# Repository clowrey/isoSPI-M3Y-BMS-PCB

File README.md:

# CellKeeper BMS — Rev1

KiCad PCB design for the **CellKeeper Battery Management System**, a replacement BMS controller for battery packs using the isoSPI protocol.

## Overview

- **MCU:** Raspberry Pi RP2354B (dual Cortex-M33 @ 150 MHz)
- **Current sensing:** TI INA228 (20-bit ADC, shunt-based)
- **Pack voltage:** 6-channel monitoring via precision dividers
- **BMB communication:** isoSPI master with galvanic isolation (Manchester encoding via PIO)
- **CAN bus:** 500 kbps, hardware transceiver
- **Contactor control:** 4-channel PWM outputs with inrush limiting
- **Input:** 12 V nominal; rated for up to 400 V DC pack voltage

## Repository Contents

| Path | Description |
|------|-------------|
| `CellKeeper.kicad_pro` | KiCad project file |
| `CellKeeper.kicad_sch` | Schematic |
| `CellKeeper.kicad_pcb` | PCB layout |
| `CellKeeper_Local.kicad_sym` / `CellKeeper_Local.pretty/` | Local symbol and footprint libraries |
| `CellKeeper.3dshapes/` | 3D models |
| `graphics/` | Silkscreen artwork and images |
| `production/` | Manufacturing outputs |
| `python_scripts/` | Utility scripts |

## Getting Started

1. Install [KiCad 10.0+](https://www.kicad.org/download/)
2. Clone this repository
3. Open `CellKeeper.kicad_pro` — project libraries load from the local `sym-lib-table` and `fp-lib-table`

## Safety

⚠️ This board interfaces with 400 V battery packs that can deliver **lethal** current. Only qualified personnel should work on high-voltage systems. This is a Rev1 development design — untested, no warranty, use at your own risk.

## Acknowledgments

- **Damien Maguire & Tom de Bree** — Original BATMan BMS software

## License

GPL-3.0 — see [LICENSE](LICENSE).

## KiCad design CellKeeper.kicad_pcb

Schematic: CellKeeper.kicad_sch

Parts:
1/2V1, 3v1, 5V1: TP; BMS_Library__TestPoint_THTPad_D1.5mm_Drill1.0mm
A1: RaspberryPi_Pico; Module__RaspberryPi_Pico_Common_Unspecified
BT1, BT2, BT3, BT4, BT5, BT6, BT7, BT8: ~100V Brick
C1, C14, C31: 680uF; Capacitor_THT__CP_Radial_D10.0mm_P5.00mm; Voltage 35V Polymer; JLCPCB Part # C46550429
C2, C10, C11, C13, C15, C16, C18, C22, C23, C28, C29, C30, C34, C35, C36, C54, C60, C89, C91, C104, C105, C106, C114: 100nF; Capacitor_SMD__C_0603_1608Metric; JLCPCB Part # C14663
C3, C4, C6, C8, C17, C32: 10uF; Capacitor_SMD__C_0805_2012Metric; Voltage 50V; JLCPCB Part # C440198
C5, C7, C12, C33, C37, C48, C49, C69: 22uF; Capacitor_SMD__C_0805_2012Metric; Voltage 25V X5R; JLCPCB Part # C45783
C9: 4.7uF; Capacitor_SMD__C_0603_1608Metric; JLCPCB Part # C19666
C19, C20, C41, C42, C67, C96, C97, C98, C99, C109, C110, C111, C112: 1uF; Capacitor_SMD__C_0603_1608Metric; JLCPCB Part # C15849
C21, C55, C116: 10uF; Capacitor_SMD__C_0805_2012Metric; Voltage 50V X5R; JLCPCB Part # C440198
C24, C25, C26, C27, C103, C113: 100pF; Capacitor_SMD__C_0603_1608Metric; JLCPCB Part # C14858
C38, C43, C68, C72: 4.7u; RP2350_80QFN_minimal__C_0402_1005Metric_small_pads; JLCPCB Part # C23733
C39, C40, C70, C71: 15pF; Capacitor_SMD__C_0402_1005Metric; JLCPCB Part # C1548
C44, C46, C47, C50, C51, C53, C56, C58, C59, C61, C63, C65, C75, C83, C84, C85, C86, C88, C90, C92, C93, C100, C101, C102: 100n; Capacitor_SMD__C_0402_1005Metric; JLCPCB Part # C1525
C45, C52, C82, C87: 4.7u; Capacitor_SMD__C_0402_1005Metric; JLCPCB Part # C23733
C62, C64: 100nf; Capacitor_SMD__C_0603_1608Metric_Pad1.08x0.95mm_HandSolder; JLCPCB Part # C14663
C66: 10uF; Capacitor_SMD__C_0805_2012Metric_Pad1.18x1.45mm_HandSolder; Voltage 50V; JLCPCB Part # C440198
C73, C74: 100nF; Capacitor_SMD__C_0603_1608Metric_Pad1.08x0.95mm_HandSolder; JLCPCB Part # C14663
C76, C77, C78, C79, C80, C81: 100nf; Capacitor_SMD__C_0603_1608Metric; JLCPCB Part # C14663
C94, C95, C107, C108: 1nF; Capacitor_SMD__C_1206_3216Metric; JLCPCB Part # C9196
Cell1, Cell2, Cell3: Battery_Cell
D1, D2, D3, D4, D5, D6, D24, D25, D26, D28, D29, D30, D31: SMB6.8CA; Diode_SMD__D_SMB; JLCPCB Part # C78395
D7, D8, D14, D19, D32, D35, D36, D43, D48: Green; LED_SMD__LED_0805_2012Metric; JLCPCB Part # C2297
D9, D10, D27, D41, D46, D49: Red; LED_SMD__LED_0805_2012Metric; JLCPCB Part # C84256
D11, D12, D15, D16, D20, D23, D37, D38, D42, D44, D47, D50: SS54; Diode_SMD__D_SMA; JLCPCB Part # C22452
D13, D17, D22, D33, D34, D45: White; LED_SMD__LED_0805_2012Metric; JLCPCB Part # C34499
D18, D21, D39, D40: SMCJ33CA; Diode_SMD__D_SMC; JLCPCB Part # C224050
F1, F3: Pyro Fuse
F2, F4: 63A HV DC
FB1, FB3, FB5: 600R@100MHz; Inductor_SMD__L_0603_1608Metric_Pad1.05x0.95mm_HandSolder; JLCPCB Part # C1002
FB2: 120Ω@100MHz; Capacitor_SMD__C_0603_1608Metric; JLCPCB Part # C14709
FL1, FL2: SDCW3225S-2-102TF; BMS_Library__FILTER-SMD_4P-L3.2-W2.5-BL; JLCPCB Part # C192586
GND1: TP; BMS_Library__TestPoint_THTPad_D1.5mm_Drill1.0mm
GPIO1, GPIO2, GPIO3: TP; BMS_Library__TestPoint_THTPad_D1.5mm_Drill1.0mm
H1, H2: MountingHole_Pad; MountingHole__MountingHole_3.7mm; not fitted
H3, H4: MountingHole_Pad; MountingHole__MountingHole_5mm; not fitted
H5, H6, H7, H8, H9, H10, H11, H12, H13: Mouse Bites 2mm; BMS_Library__mouse-bite-2mm-slot-min
H14, H15: MountingHole_Pad; MountingHole__MountingHole_8.4mm_M8_Pad_Via
J1: Screw_Terminal_01x04; BMS_Library__PhoenixContact_MC_1_5_4-G-3.81_1x04_P3.81mm_Ho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
J2: Screw_Terminal_01x01; BMS_Library__XFCN_T34008_M3_Terminal_Frame_PCB; JLCPCB Part # C481446
J3, J7, J15: Screw_Terminal_01x04; BMS_Library__PhoenixContact_MC_1_5_4-G-3.81_1x04_P3.81mm_Ho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; not fitted
J4, J5: 8P8C_LED_Shielded_x2; Connector_RJ__RJ45_HCTL_HC-RJ45-5JA-2-2-Y; JLCPCB Part # C3010546
J6: OEM Connector; BMS_Library__S44BRAD1AK; Mfr. # S44B-RAD1AK
J8, J16: Conn_01x03; Connector_PinHeader_2.54mm__PinHeader_1x03_P2.54mm_Vertical; not fitted
J9, J11, J19: USB_C_Receptacle_USB2.0_16P; BMS_Library__USB_C_Receptacle_HRO_TYPE-C-31-M-12; JLCPCB Part # C2765186
J10: 3.81P Screw Terminal; BMS_Library__PhoenixContact_MC_1_5_8-G-3.81_1x08_P3.81mm_Ho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; not fitted
J12, J22: Conn_02x10_Odd_Even; Connector_PinHeader_2.54mm__PinHeader_2x10_P2.54mm_Vertical; not fitted
J13: USB_C_Receptacle_USB2.0_16P
J14: OEM Shunt Connector; BMS_Library__CONN_ZE05H-8DP-2H_HIR; MFR.Part # ZE05H-8DP-2H; JLCPCB Part # C17284895
J17: OEM HV Sense Connector; BMS_Library__CONN_173864-1_TYC_Empty_Pins; MFR Part # 173864-1; JLCPCB Part # C573648
J18: 7.62mm Pitch Screw Terminal; Connector_Phoenix_GMSTB__PhoenixContact_GMSTBA_2_5_6-G-7_62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; not fitted
J20, J23: OEM Connector; BMS_Library__CONN_SD-34912-001_02_MOL; MFR.Part # 349128020; JLCPCB Part # C587318
J21, J24: 3.81P Screw Terminal; BMS_Library__PhoenixContact_MC_1_5_2-G-3.81_1x02_P3.81mm_Ho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; not fitted
JP1, JP2, JP3, JP4, JP7, JP8, JP9, JP12, JP13, JP14, JP16, JP17, JP18, JP19, JP20, JP21, JP22, JP23, JP24, JP27, JP28, JP29, JP30, JP31, JP32, JP33, JP34, JP35, JP37: 0r; BMS_Library__J_0603_jumper; JLCPCB Part # C21189; not fitted
JP5, JP6, JP10, JP11, JP15, JP36: 0r; BMS_Library__J_0603_jumper; JLCPCB Part # C21189
JP25, JP26: jumper-bridged; Jumper__SolderJumper-2_P1.3mm_Bridged_RoundedPad1.0x1.5mm
K1, K6: Link Positive
K2, K7: Link Negative
K3, K9: FC Positive
K4, K8: FC Negative
K5, K10: Inverter
L1, L5: 6.8uh; Inductor_SMD__L_Changjiang_FXL0630; JLCPCB Part # C167221
L2, L3: 22uh 5.5A; Inductor_SMD__L_Changjiang_FXL1040; JLCPCB Part # C475917
L4, L6: 3.3uh; RP2350_80QFN_minimal__L_pol_2016; JLCPCB Part # C42411119
Q1, Q2, Q3, Q4: BSC0805LS; BMS_Library__TDSON-8_5x6_; JLCPCB Part # C534374
R1, R2, R11, R16, R29, R33, R35, R39, R40, R41, R96, R97, R98, R99, R100, R101, R140: 24k; Resistor_SMD__R_0603_1608Metric; JLCPCB Part # C23352
R3, R4, R15, R17, R19, R20, R21, R25, R28, R42, R50, R84: 10k; Resistor_SMD__R_0603_1608Metric; JLCPCB Part # C25804
R5, R10, R18, R24, R34, R36, R151, R152: 100k; Resistor_SMD__R_0603_1608Metric; JLCPCB Part # C25803
R7, R12, R37, R38: 33R; Resistor_SMD__R_0603_1608Metric; JLCPCB Part # C23140
R8, R9, R22, R23, R46, R47, R48, R49, R133, R134, R141: 1k; Resistor_SMD__R_0603_1608Metric; JLCPCB Part # C21190
R13, R14, R51, R52: 10k; Resistor_SMD__R_0603_1608Metric_Pad0.98x0.95mm_HandSolder; JLCPCB Part # C25804
R26: 3.3k; Resistor_SMD__R_0402_1005Metric; JLCPCB Part # C25890
R27, R53, R55, R56, R74, R92, R94, R95, R129, R130, R131, R132, R135: 1k; Resistor_SMD__R_0402_1005Metric; JLCPCB Part # C11702
R30, R73: 510r; Resistor_SMD__R_0603_1608Metric; JLCPCB Part # C23193
R31, R32: 120r; Resistor_SMD__R_1206_3216Metric; JLCPCB Part # C17909
R43, R44: 2.2k; Resistor_SMD__R_0603_1608Metric; JLCPCB Part # C4190
R45, R57, R66, R69, R72, R77, R79, R80, R81, R82, R83, R85, R89, R90, R138, R139, R143, R144: 5.1k; Resistor_SMD__R_0603_1608Metric; JLCPCB Part # C23186
R54, R68, R93, R126: 33r; Resistor_SMD__R_0402_1005Metric; JLCPCB Part # C25105
R58, R59, R60, R61, R62, R63, R64, R65: 18r
R67: 12.24R
R70, R71, R127, R128: 22R; Resistor_SMD__R_0402_1005Metric; JLCPCB Part # C25092
R75: 47k; Resistor_SMD__R_0603_1608Metric; JLCPCB Part # C25819; not fitted
R76: 0r; Resistor_SMD__R_0603_1608Metric; JLCPCB Part # C21189
R86, R147: 25296nΩ
R87, R88: 220r; Resistor_SMD__R_0603_1608Metric; JLCPCB Part # C22962
R91: 27R 50W
R102, R103, R104, R105, R106, R107, R108, R109, R110, R111, R112, R113, R114, R115, R116, R117, R118, R119, R120, R121, R122, R123, R124, R125: 3M; Resistor_SMD__R_1206_3216Metric; JLCPCB Part # C488822
R136, R137, R148, R149: 47r; Resistor_SMD__R_0603_1608Metric; JLCPCB Part # C23182
R142, R150: 100R; Resistor_SMD__R_0603_1608Metric; JLCPCB Part # C22775
R145, R146: 1M; Resistor_SMD__R_1206_3216Metric; JLCPCB Part # C17927
RevisionS1: TP; BMS_Library__TestPoint_THTPad_D1.5mm_Drill1.0mm
SW1, SW2, SW3, SW4: TS-1187A-B-A-B; Button_Switch_SMD__SW_Push_1P1T_XKB_TS-1187A; JLCPCB Part # C318884
TH1, TH2, TH3, TH4, TH5, TH6: B59451C1130B070; BMS_Library__RV_Disc_D15.5mm_W7.5mm_P5.0mm; JLCPCB Part # C2762811
TP1, TP2, TP4, TP6, TP7, TP8, TP9, TP10, TP15, TP23, TP24, TP25, TP34, TP35, TP36, TP37, TP43, TP44, TP45, TP46, TP47, TP48: TestPoint_2Pole; BMS_Library__TestPoint_2Pads_Pitch2.54mm_Pad1.5_Drill1.0mm
TP3, TP5, TP11, TP12, TP13, TP14, TP16, TP17, TP18, TP19, TP20, TP21, TP22, TP26, TP27, TP28, TP29, TP30, TP31, TP32, TP33, TP38, TP39, TP40, TP41, TP49: TP; BMS_Library__TestPoint_THTPad_D1.5mm_Drill1.0mm
TP42: TestPoint_2Pole; BMS_Library__TestPoint_2Pads_Pitch2.54mm_Pad1.5_Drill1.0mm; not fitted
TR1, TR2: HM2113ZNLT; BMS_Library__HM2113ZNLT; JLCPCB Part # C5730533
U1, U11: UCC27524DR; Package_SO__SOIC-8_3.9x4.9mm_P1.27mm; JLCPCB Part # C465729
U3: TPS5430DDAR; Package_SO__TI_SO-PowerPAD-8_ThermalVias; LCSC Part C9864
U4, U15: F0505S-1WR3; BMS_Library__H0505S-1WR2; JLCPCB Part # C7465182
U5, U10: ISO1050DUB; Package_SO__SOP-8_6.62x9.15mm_P2.54mm; LCSC Part # C16428
U6, U7, U8, U9, U12, U13: LTV-217-B-G; Package_SO__SSOP-4_4.4x2.6mm_P1.27mm; JLCPCB Part # C115450
U14, U20: RP2354B; RP2350_80QFN_minimal__RP2350-QFN-80-1EP_10x10_P0.4mm_EP3.4x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; JLCPCB Part # C39843328
U16: ISO1540; Package_SO__SOIC-8_3.9x4.9mm_P1.27mm; JLCPCB Part # C179739
U17: INA228; Package_SO__TSSOP-10_3x3mm_P0.5mm; JLCPCB Part # C5214669
U18, U19: ADS1115; Package_SO__TSSOP-10_3x3mm_P0.5mm; LCSC Part # C37593
U21, U23: SP3485EN-L/TR; Package_SO__SOIC-8_3.9x4.9mm_P1.27mm; JLCPCB Part # C8963
U22, U24: AM26LV32EIDR; Package_SO__SOIC-16_3.9x9.9mm_P1.27mm; JLCPCB Part # C527448
U25, U26: TLV1117LV33DCYR; Package_TO_SOT_SMD__SOT-223-3_TabPin2; JLCPCB Part # C15578
Y1, Y2: ABM8-272-T3; Crystal__Crystal_SMD_3225-4Pin_3.2x2.5mm; JLCPCB Part # C20625731

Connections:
3.3V Sense: C22.2, R20.2, R21.1, U14.49 (GPIO40_ADC0)
5V Sense: C36.2, R41.2, R42.1, U14.52 (GPIO41_ADC1)
+1V1: C43.1, C44.1, C46.1, C47.1, L4.1, U14.10 (DVDD), U14.32 (DVDD), U14.51 (DVDD), U14.65 (VREG_FB)
+1V1_2: C72.1, C75.1, C83.1, C84.1, L6.1, U20.10 (DVDD), U20.32 (DVDD), U20.51 (DVDD), U20.65 (VREG_FB)
+3.3V: C9.2, C10.1, C11.1, C38.1, C50.1, C51.1, C53.1, C56.1, C58.1, C59.1, C61.1, C63.1, C65.1, C66.2, C68.1, C85.1, C86.1, C88.1, C89.1, C90.1, C91.2, C92.1, C93.1, C100.1, C101.1, C102.1, D7.2 (A), D9.2 (A), D41.2 (A), D43.2 (A), FB5.1, J3.1, J12.5, J12.7, J12.9, J22.5, J22.7, J22.9, JP35.2, R2.1, R4.1, R15.1, R20.1, R28.1, R29.1, R54.2, R57.1, R66.1, R68.2, R75.1, R89.1, R90.1, R93.2, R126.2, R135.1, TP4.2, U5.1 (VCC1), U6.4, U7.4, U10.1 (VCC1), U12.4, U13.4, U14.5 (IOVDD), U14.15 (IOVDD), U14.24 (IOVDD), U14.29 (IOVDD), U14.41 (IOVDD), U14.50 (IOVDD), U14.60 (IOVDD), U14.64 (VREG_VIN), U14.68 (USB_OTP_VDD), U14.69 (QSPI_IOVDD), U14.76 (IOVDD), U16.1 (VCC1), U20.5 (IOVDD), U20.15 (IOVDD), U20.24 (IOVDD), U20.29 (IOVDD), U20.41 (IOVDD), U20.50 (IOVDD), U20.60 (IOVDD), U20.64 (VREG_VIN), U20.68 (USB_OTP_VDD), U20.69 (QSPI_IOVDD), U20.76 (IOVDD), U21.8 (VCC), U22.4 (G), U22.16 (VDD), U25.2 (VO)
+3.3V2: A1.36 (3V3), C105.1, C106.2, U23.8 (VCC), U24.4 (G), U24.16 (VDD)
+3.3VSen: 3v1.1 (1_1), C67.2, C73.2, C74.2, FB5.2, R87.1, U18.8 (VDD), U19.1 (ADDR), U19.8 (VDD)
+5V: C2.2, C3.2, C7.2, C18.2, C29.2, C31.1, C32.2, C33.2, C37.2, C41.2, C42.2, C48.2, D50.2 (A), FB2.2, J12.1, J12.3, J22.1, J22.3, L1.2, L3.1, L5.2, R26.1, R35.1, R41.1, TP9.2, U1.6 (V_{DD}), U10.8 (VCC2), U11.6 (V_{DD}), U12.1, U13.1
+LDO_IN: C5.2, D44.1 (K), D47.1 (K), D50.1 (K), U25.3 (VI)
/Blue: J4.4, JP15.2, JP16.1, JP18.1
/Brown: J4.8, JP19.2, JP20.1, JP23.1
/CAN2 H: C26.2, D30.2 (A2), FL2.2, J5.4, J5.16, R32.2, TP8.2
/CAN2 L: C27.1, D31.1 (A1), FL2.3, J5.5, J5.17, JP5.1, TP8.1
/CAN 5V: 5V1.1 (1_1), C28.2, FB1.2, R22.2, R30.1, R33.1, R43.2, U5.8 (VCC2)
/CAN H: C24.2, D28.2 (A2), FL1.2, JP3.1, JP7.1, JP9.1, JP13.1, JP15.1, JP19.1, JP21.1, JP27.1, JP36.1, TP7.2
/CAN L: C25.1, D29.1 (A1), FL1.3, JP4.2, JP8.2, JP10.2, JP14.2, JP16.2, JP20.2, JP22.2, JP28.2, R31.1, TP7.1
/Contactor_Input: D1.2 (A2), D11.2 (A), D12.2 (A), J1.3
/FC Neg: H15.1 (1_1), K4.13, K8.13, K10.2, TH4.2, TH5.2, TH6.2
/FC-CTR-NEG-AUX-D: J6.17, J7.2, R47.1
/FC-CTR-POS-AUX-D: J6.18, J7.1, R46.1
/FC-Neg-Jumper: C35.2, D36.1 (K), D38.2 (A), D40.2 (A2), JP25.1 (A), JP26.1 (A), Q4.5 (D)
/FC-Pos-Jumper: C13.2, D14.1 (K), D16.2 (A), D18.2 (A2), JP1.1, JP2.1, Q1.5 (D)
/GPIO0: R74.2, U14.77 (GPIO0)
/GPIO3: J12.2, U14.80 (GPIO3)
/GPIO25: R85.1, U14.26 (GPIO25)
/GPIO44_ADC4: GPIO1.1 (1_1), U14.55 (GPIO44_ADC4)
/GPIO45_ADC5: GPIO2.1 (1_1), U14.56 (GPIO45_ADC5)
/GPIO46_ADC6: GPIO3.1 (1_1), U14.57 (GPIO46_ADC6)
/GPIO47_ADC7: R75.2, R76.1, RevisionS1.1 (1_1), U14.58 (GPIO47_ADC7)
/Grn: J4.6, JP7.2, JP8.1, JP11.1
/Logic_Input: D4.2 (A2), D15.2 (A), J1.4, R151.2
/MCU2_GPIO0: R135.2, U20.77 (GPIO0)
/MCU2_GPIO1: R131.2, U20.78 (GPIO1)
/MCU2_GPIO2: R132.2, U20.79 (GPIO2)
/MCU2_GPIO3: J22.2, U20.80 (GPIO3)
/MCU2_GPIO4: J22.4, U20.1 (GPIO4)
/MCU2_GPIO5: J22.6, U20.2 (GPIO5)
/MCU2_GPIO6: J22.8, R133.1, U20.3 (GPIO6)
/MCU2_GPIO7: J22.10, U20.4 (GPIO7)
/MCU2_GPIO8: J22.12, R134.1, U20.6 (GPIO8)
/MCU2_GPIO9: J22.14, U20.7 (GPIO9)
/MCU2_GPIO10: J22.16, U20.8 (GPIO10)
/MCU2_GPIO12: J22.20, U20.11 (GPIO12)
/MCU2_GPIO13: U20.12 (GPIO13)
/MCU2_GPIO14: R140.1, R141.1, U20.13 (GPIO14)
/MCU2_GPIO15: U20.14 (GPIO15)
/MCU2_GPIO16: U20.16 (GPIO16)
/MCU2_GPIO17: U20.17 (GPIO17)
/MCU2_GPIO18: U20.18 (GPIO18)
/MCU2_GPIO19: U20.19 (GPIO19)
/MCU2_GPIO20: U20.20 (GPIO20)
/MCU2_GPIO21: U20.21 (GPIO21)
/MCU2_GPIO22: U20.22 (GPIO22)
/MCU2_GPIO23: U20.23 (GPIO23)
/MCU2_GPIO24: U20.25 (GPIO24)
/MCU2_GPIO25: R143.1, U20.26 (GPIO25)
/MCU2_GPIO26: U20.27 (GPIO26)
/MCU2_GPIO27: U20.28 (GPIO27)
/MCU2_GPIO33: U20.42 (GPIO33)
/MCU2_GPIO34: U20.43 (GPIO34)
/MCU2_GPIO35: U20.44 (GPIO35)
/MCU2_GPIO36: U20.45 (GPIO36)
/MCU2_GPIO37: U20.46 (GPIO37)
/MCU2_GPIO38: R129.2, U20.47 (GPIO38)
/MCU2_GPIO39: R130.2, U20.48 (GPIO39)
/Orange: J4.2, JP21.2, JP22.1, JP24.1
/PH: C16.1, D23.1 (K), L3.2, U3.8 (PH)
/QSPI2_SCLK: U20.71 (QSPI_SCLK)
/QSPI2_SD0: U20.72 (QSPI_SD0)
/QSPI2_SD1: U20.74 (QSPI_SD1)
/QSPI2_SD2: U20.73 (QSPI_SD2)
/QSPI2_SD3: U20.70 (QSPI_SD3)
/QSPI2_SS: R94.1, U20.75 (QSPI_SS)
/QSPI_SCLK: U14.71 (QSPI_SCLK)
/QSPI_SD0: U14.72 (QSPI_SD0)
/QSPI_SD1: U14.74 (QSPI_SD1)
/QSPI_SD2: U14.73 (QSPI_SD2)
/QSPI_SD3: U14.70 (QSPI_SD3)
/QSPI_SS: R55.1, U14.75 (QSPI_SS)
/RUN: R56.2, SW2.2, TP14.1 (1_1)
/RUN_2: R95.1, U20.35 (RUN)
/SWCLK: J8.1, U14.33 (SWCLK)
/SWCLK_2: J16.1, U20.33 (SWCLK)
/SWD: J8.3, U14.34 (SWD)
/SWD_2: J16.3, U20.34 (SWD)
/Serial API 5V Diode: D42.1 (K), J9.A4 (VBUS), J9.A9 (VBUS), J9.B4 (VBUS), J9.B9 (VBUS), TP13.1 (1_1)
/Serial API RX: J9.A7 (D-), J9.B7 (D-), R48.1, R50.2, TP10.1
/Serial API TX: J9.A6 (D+), J9.B6 (D+), R49.1, TP10.2
/USB2_D+: J19.A6 (D+), J19.B6 (D+), R127.1, TP39.1 (1_1)
/USB2_D-: J19.A7 (D-), J19.B7 (D-), R128.1, TP40.1 (1_1)
/USB_D+: J11.A6 (D+), J11.B6 (D+), R70.1, TP20.1 (1_1)
/USB_D-: J11.A7 (D-), J11.B7 (D-), R71.1, TP21.1 (1_1)
/VREG2_AVDD: C82.1, R93.1, U20.61 (VREG_AVDD)
/VREG2_LX: L6.2, U20.63 (VREG_LX)
/VREG_AVDD: C45.1, R54.1, U14.61 (VREG_AVDD)
/VREG_LX: L4.2, U14.63 (VREG_LX)
/V_cont1: C8.2, D11.1 (K), D12.1 (K), L2.2
/Wht-Blue: J4.5, JP9.2, JP10.1, JP12.1
/Wht-Brown: J4.7, JP13.2, JP14.1, JP17.1
/Wht-Grn: J4.3, JP3.2, JP4.1, JP6.1
/Wht-Org: J4.1, JP27.2, JP28.1, JP29.1
/XIN: C39.1, U14.30 (XIN), Y1.1
/XIN_2: C70.1, U20.30 (XIN), Y2.1
/XOUT: R53.1, U14.31 (XOUT)
/XOUT_2: R92.1, U20.31 (XOUT)
/iso2+: C109.1, C112.1, C113.2, R148.2, R150.1, TP48.1, TR2.1 (TD-)
/iso2-: C110.1, C111.1, C113.1, R149.2, R150.2, TP48.2, TR2.3 (TD+)
/iso+: C96.1, C99.1, C103.2, R136.2, R142.1, TP42.1, TR1.1 (TD-)
/iso-: C97.1, C98.1, C103.1, R137.2, R142.2, TP42.2, TR1.3 (TD+)
Batt Negative: J17.10, J18.6, R121.2
Batt Positive: J17.1, J18.1, R120.2
C FC-Neg (GND): J6.37, J10.2, JP25.2 (B), JP26.2 (B)
C FC-Pos (GND): J6.36, J10.4, JP1.2, JP2.2
C Neg (GND): C34.2, D35.1 (K), D37.2 (A), D39.2 (A2), J6.42, J10.6, Q3.5 (D)
C Pos (GND): C15.2, D19.1 (K), D20.2 (A), D21.2 (A2), J6.41, J10.8, Q2.5 (D)
CAN2 Rx: D8.1 (K), J12.6, TP2.1, U10.2 (RXD), U14.2 (GPIO5)
CAN2 Tx: D10.1 (K), J12.4, TP2.2, U10.3 (TXD), U14.1 (GPIO4)
CAN Rx: R1.2, TP1.1, U5.2 (RXD), U14.20 (GPIO20)
CAN Tx: R3.2, TP1.2, U5.3 (TXD), U14.19 (GPIO19)
CTR-FC-NEG: R83.1, U11.4 (INB), U14.14 (GPIO15)
CTR-FC-Pos: R82.1, U1.4 (INB), U14.16 (GPIO16)
CTR-LNK-NEG: R81.1, U11.2 (INA), U14.17 (GPIO17)
CTR-LNK-POS: R77.1, U1.2 (INA), U14.18 (GPIO18)
CTR_EN: R141.2, R144.1, U1.1 (ENA), U1.8 (ENB), U11.1 (ENA), U11.8 (ENB)
Drive Unit Neg: H14.1 (1_1), K2.13, K4.14, K5.2, K7.13, K8.14, TH1.1, TH2.1, TH3.1
Emergency Stop: J12.18, J22.18, R13.2, U6.3, U14.9 (GPIO11), U20.9 (GPIO11)
Extra Input: J12.20, R14.2, U7.3, U14.11 (GPIO12)
Extra Output 1: R8.1, U14.12 (GPIO13)
Extra Output 2: R9.1, U14.13 (GPIO14)
FC Negative: J17.7, J18.4, R123.2
FC Positive: J17.4, J18.3, R122.2
FC-CTR-NEG-AUX: J12.16, R52.2, U13.3, U14.8 (GPIO10)
FC-CTR-POS-AUX: J12.14, R51.2, U12.3, U14.7 (GPIO9)
GND: C1.2, C2.1, C3.1, C4.1, C5.1, C6.1, C7.1, C8.1, C9.1, C10.2, C11.2, C12.1, C13.1, C14.2, C15.1, C17.1, C18.1, C22.1, C23.1, C26.1, C27.2, C29.1, C30.1, C31.2, C32.1, C33.1, C34.1, C35.1, C36.1, C37.1, C38.2, C39.2, C40.2, C43.2, C44.2, C45.2, C46.2, C47.2, C48.1, C49.1, C50.2, C51.2, C52.2, C53.2, C56.2, C58.2, C59.2, C61.2, C63.2, C65.2, C66.1, C67.1, C68.2, C69.1, C70.2, C71.2, C72.2, C73.1, C74.1, C75.2, C82.2, C83.2, C84.2, C85.2, C86.2, C87.2, C88.2, C89.2, C90.2, C91.1, C92.2, C93.2, C100.2, C101.2, C102.2, C104.1, D3.1 (A1), D6.1 (A1), D13.1 (K), D17.1 (K), D18.1 (A1), D21.1 (A1), D22.1 (K), D23.2 (A), D26.1 (A1), D30.1 (A1), D31.2 (A2), D34.1 (K), D39.1 (A1), D40.1 (A1), D46.1 (K), D48.1 (K), D49.1 (K), GND1.1 (1_1), J1.1, J1.2, J2.1 (Pin_1_1), J3.4, J5.3, J5.6, J5.15, J5.18, J5.SH, J6.3, J6.4, J6.30, J7.3, J7.4, J8.2, J9.A1 (GND), J9.A12 (GND), J9.B1 (GND), J9.B12 (GND), J9.SH (SHIELD), J11.A1 (GND), J11.A12 (GND), J11.B1 (GND), J11.B12 (GND), J11.SH (SHIELD), J12.11, J12.13, J12.15, J12.17, J12.19, J16.2, J19.A1 (GND), J19.A12 (GND), J19.B1 (GND), J19.B12 (GND), J19.SH (SHIELD), J22.11, J22.13, J22.15, J22.17, J22.19, Q1.1 (S), Q1.2 (S), Q1.3 (S), Q2.1 (S), Q2.2 (S), Q2.3 (S), Q3.1 (S), Q3.2 (S), Q3.3 (S), Q4.1 (S), Q4.2 (S), Q4.3 (S), R5.1, R10.1, R13.1, R14.1, R19.2, R21.2, R25.2, R27.2, R34.1, R36.1, R42.2, R51.1, R52.1, R74.1, R76.2, R77.2, R79.1, R80.1, R81.2, R82.2, R83.2, R88.2, R138.1, R139.1, R144.2, R146.1, SW1.1, SW2.1, SW3.1, SW4.1, TP3.1 (1_1), TP4.1, TP9.1, TP11.1 (1_1), TP16.1 (1_1), TP19.1 (1_1), TP23.1, TP24.1, TP38.1 (1_1), TP43.1, TP44.1, U1.3 (GND), U3.6 (GND), U3.9 (PowerPAD), U4.2 (-Vin), U5.4 (GND1), U8.2, U9.2, U10.4 (GND1), U10.5 (GND2), U11.3 (GND), U14.62 (VREG_PGND), U14.81 (GND), U15.2 (-Vin), U16.4 (GND1), U18.1 (ADDR), U18.3 (GND), U19.3 (GND), U20.62 (VREG_PGND), U20.81 (GND), U21.2 (~RE), U21.5 (GND), U22.8 (GND), U22.12 (~G), U25.1 (GND), Y1.2, Y1.4, Y2.2, Y2.4
GND2: A1.3 (GND), A1.8 (GND), A1.13 (GND), A1.18 (GND), A1.23 (GND), A1.28 (GND), A1.38 (GND), C105.2, C106.1, C114.1, U23.2 (~RE), U23.5 (GND), U24.8 (GND), U24.12 (~G)
GND CAN: C21.1, C24.1, C25.2, C28.1, D28.1 (A1), D29.2 (A2), D33.1 (K), J4.19, J4.SH, JP6.2, JP11.2, JP12.2, JP17.2, JP18.2, JP23.2, JP24.2, JP29.2, JP37.2, R30.2, TP5.1 (1_1), U4.5 (-Vout), U5.5 (GND2)
GND Shunt NTC -: C54.1, C55.1, C60.1, C64.1, C116.1, D45.1 (K), J14.1, J14.3, J15.2, R73.2, TP17.1 (1_1), U15.5 (-Vout), U16.5 (GND2), U17.1 (A1), U17.2 (A0), U17.7 (GND), U26.1 (GND); also elsewhere on the board
HMI Serial RX: R48.2, R130.1, U14.48 (GPIO39)
HMI Serial TX: R45.2, R49.2, R129.1, U14.47 (GPIO38)
I2C SCL Shunt: R57.2, TP15.2, U14.21 (GPIO21), U16.3 (SCL1)
I2C SCL Vsense: R90.2, TP25.2, U14.23 (GPIO23), U18.10 (SCL), U19.10 (SCL)
I2C SDA Shunt: R66.2, TP15.1, U14.25 (GPIO24), U16.2 (SDA1)
I2C SDA Vsense: R89.2, TP25.1, U14.22 (GPIO22), U18.9 (SDA), U19.9 (SDA)
IsoSPI2 RX H: A1.11 (GPIO8), TP46.1, U24.5 (2Y)
IsoSPI2 RX L: A1.12 (GPIO9), TP46.2, U24.3 (1Y)
IsoSPI2 TX Data: A1.10 (GPIO7), TP45.2, U23.4 (DI)
IsoSPI2 TX En: A1.9 (GPIO6), TP45.1, U23.3 (DE)
IsoSPI2+: J23.1, J24.1, TR2.4 (TX+)
IsoSPI2-: J23.2, J24.2, TR2.6 (TX-)
IsoSPI RX Debug: TP24.2, U14.39 (GPIO31)
IsoSPI RX Debug 2: TP43.2, U20.39 (GPIO31)
IsoSPI RX H: TP35.1, U14.36 (GPIO28), U20.36 (GPIO28), U22.5 (2Y)
IsoSPI RX L: TP35.2, U14.37 (GPIO29), U20.37 (GPIO29), U22.3 (1Y)
IsoSPI TX Data: TP34.2, U14.28 (GPIO27), U21.4 (DI)
IsoSPI TX En: TP34.1, U14.27 (GPIO26), U21.3 (DE)
IsoSPI+: J20.1, J21.1, TR1.4 (TX+)
IsoSPI-: J20.2, J21.2, TR1.6 (TX-)
Link Negative: J17.22, J18.5, R124.2
Link Positive: J17.13, J18.2, R125.2
MAIN-SUP TX/RX: R131.1, TP36.1, U14.79 (GPIO2)
MAX RX: J12.8, R133.2, U14.3 (GPIO6), U22.13 (4Y)
MAX RX2: A1.7 (GPIO5), U24.13 (4Y)
unnamed: BT1.1 (+), BT5.1 (+), K1.14, K6.14, R91.1
unnamed: BT1.2 (-), BT2.1 (+)
unnamed: BT2.2 (-), R86.2
unnamed: BT3.1 (+), F1.1
unnamed: BT3.2 (-), BT4.1 (+)
unnamed: BT4.2 (-), BT8.2 (-), K2.14, K7.14
unnamed: BT5.2 (-), BT6.1 (+)
unnamed: BT6.2 (-), R147.1
unnamed: BT7.1 (+), F3.1
unnamed: BT7.2 (-), BT8.1 (+)
unnamed: C19.1, J4.20, J4.21, JP37.1, U6.2
unnamed: C19.2, R22.1, U6.1
unnamed: C20.1, J4.14, J4.23, U7.2
unnamed: C20.2, R23.1, U7.1
unnamed: C40.1, R53.2, Y1.3
unnamed: C41.1, R46.2, U12.2
unnamed: C42.1, R47.2, U13.2
unnamed: C71.1, R92.2, Y2.3
unnamed: C94.1, TP37.2
unnamed: C95.1, TP37.1
unnamed: C107.1, TP47.2
unnamed: C108.1, TP47.1
unnamed: Cell1.1 (+), R58.1, R59.1
unnamed: Cell1.2 (-), Cell2.1 (+), R60.1, R61.1
unnamed: Cell2.2 (-), Cell3.1 (+), R62.1, R63.1
unnamed: Cell3.2 (-), R64.1, R65.1
unnamed: D1.1 (A1), D2.2 (A2)
unnamed: D2.1 (A1), D3.2 (A2)
unnamed: D4.1 (A1), D5.2 (A2)
unnamed: D5.1 (A1), D6.2 (A2)
unnamed: D7.1 (K), R1.1
unnamed: D8.2 (A), R2.2
unnamed: D9.1 (K), R3.1
unnamed: D10.2 (A), R4.2
unnamed: D13.2 (A), R151.1
unnamed: D14.2 (A), R11.2
unnamed: D17.2 (A), R15.2
unnamed: D19.2 (A), R16.2
unnamed: D22.2 (A), R152.1
unnamed: D24.1 (A1), D25.2 (A2)
unnamed: D25.1 (A1), D26.2 (A2)
unnamed: D27.2 (A), R28.2
unnamed: D32.2 (A), R29.2
unnamed: D33.2 (A), R33.2
unnamed: D34.2 (A), R35.2
unnamed: D35.2 (A), R39.2
unnamed: D36.2 (A), R40.2
unnamed: D41.1 (K), R45.1
unnamed: D42.2 (A), FB2.1
unnamed: D43.1 (K), R50.1
unnamed: D44.2 (A), J11.A4 (VBUS), J11.A9 (VBUS), J11.B4 (VBUS), J11.B9 (VBUS), TP22.1 (1_1)
unnamed: D45.2 (A), R17.2
unnamed: D46.2 (A), R85.2
unnamed: D47.2 (A), J19.A4 (VBUS), J19.A9 (VBUS), J19.B4 (VBUS), J19.B9 (VBUS), TP41.1 (1_1)
unnamed: D48.2 (A), R140.2
unnamed: D49.2 (A), R143.2
unnamed: F1.2, R86.1
unnamed: F2.1, F4.1, K1.13, K3.14, K6.13, K9.14
unnamed: F2.2, K5.1
unnamed: F3.2, R147.4
unnamed: F4.2, K3.13, K9.13, K10.1, R91.2
unnamed: J4.13, R23.2, R44.2
unnamed: J4.15, U9.4
unnamed: J4.16, U8.3
unnamed: J4.17, U8.4
unnamed: J4.18, U9.3
unnamed: J4.22, R43.1
unnamed: J4.24, R44.1
unnamed: J6.1, JP30.2
unnamed: J6.2, JP31.2
unnamed: J6.5, JP32.2
unnamed: J6.6, JP33.2
unnamed: J6.15, JP34.2
unnamed: J6.29, JP35.1
unnamed: J11.A5 (CC1), R79.2
unnamed: J11.B5 (CC2), R80.2
unnamed: J13.A1 (GND), J13.A12 (GND), J13.B1 (GND), J13.B12 (GND)
unnamed: J13.A4 (VBUS), J13.A9 (VBUS), J13.B4 (VBUS), J13.B9 (VBUS)
unnamed: J19.A5 (CC1), R138.2
unnamed: J19.B5 (CC2), R139.2
unnamed: JP5.2, R32.1
unnamed: JP36.2, R31.2
unnamed: Q1.4 (G), R7.2
unnamed: Q2.4 (G), R12.2
unnamed: Q3.4 (G), R37.2
unnamed: Q4.4 (G), R38.2
unnamed: R8.2, U8.1
unnamed: R9.2, U9.1
unnamed: R55.2, SW1.2, TP12.1 (1_1)
unnamed: R58.2, R59.2
unnamed: R60.2, R61.2, R67.2
unnamed: R62.2, R63.2, R67.1
unnamed: R64.2, R65.2
unnamed: R94.2, SW3.2, TP26.1 (1_1)
unnamed: R95.2, SW4.2, TP30.1 (1_1)
unnamed: R102.2, R108.1
unnamed: R103.2, R109.1
unnamed: R104.2, R110.1
unnamed: R105.2, R111.1
unnamed: R106.2, R112.1
unnamed: R107.2, R113.1
unnamed: R108.2, R114.1
unnamed: R109.2, R115.1
unnamed: R110.2, R116.1
unnamed: R111.2, R117.1
unnamed: R112.2, R118.1
unnamed: R113.2, R119.1
unnamed: R114.2, R120.1
unnamed: R115.2, R121.1
unnamed: R116.2, R122.1
unnamed: R117.2, R123.1
unnamed: R118.2, R124.1
unnamed: R119.2, R125.1
unnamed: R145.1, R146.2
unnamed: TH1.2, TH4.1
unnamed: TH2.2, TH5.1
unnamed: TH3.2, TH6.1
unnamed: C104.2, TR1.2 (C_TD)
unnamed: R145.2, TR1.5 (C_TX)
unnamed: C114.2, TR2.2 (C_TD)
unnamed: R10.2, R12.1, U1.7 (OUTA)
unnamed: R5.2, R7.1, U1.5 (OUTB)
unnamed: C16.2, U3.1 (BOOT)
unnamed: R26.2, R27.1, U3.4 (VSENSE)
unnamed: C12.2, L1.1, U4.1 (+Vin)
unnamed: C21.2, FB1.1, U4.7 (+Vout)
unnamed: FL1.1, U5.7 (CANH)
unnamed: FL1.4, U5.6 (CANL)
unnamed: FL2.1, U10.7 (CANH)
unnamed: FL2.4, U10.6 (CANL)
unnamed: R34.2, R37.1, U11.7 (OUTA)
unnamed: R36.2, R38.1, U11.5 (OUTB)
unnamed: C52.1, R68.1, U14.59 (ADC_AVDD)
unnamed: R56.1, U14.35 (RUN)
unnamed: R71.2, U14.66 (USB_DM)
unnamed: R70.2, U14.67 (USB_DP)
unnamed: C49.2, L5.1, U15.1 (+Vin)
unnamed: C55.2, FB3.1, U15.7 (+Vout)
unnamed: R72.2, U16.6 (SCL2), U17.5 (SCL)
unnamed: R69.2, U16.7 (SDA2), U17.4 (SDA)
unnamed: C76.2, R96.1, R102.1, TP31.1 (1_1), U18.4 (AIN0), U19.6 (AIN2)
unnamed: C77.1, R97.2, R103.1, TP29.1 (1_1), U18.5 (AIN1)
unnamed: C78.2, R98.1, R104.1, TP33.1 (1_1), U18.6 (AIN2), U19.5 (AIN1)
unnamed: C79.1, R99.1, R105.1, TP27.1 (1_1), U18.7 (AIN3)
unnamed: C80.2, R100.1, R106.1, TP32.1 (1_1), U19.4 (AIN0)
unnamed: C81.1, R101.1, R107.1, TP28.1 (1_1), U19.7 (AIN3)
unnamed: C87.1, R126.1, U20.59 (ADC_AVDD)
unnamed: R128.2, U20.66 (USB_DM)
unnamed: R127.2, U20.67 (USB_DP)
unnamed: R136.1, U21.6 (A)
unnamed: R137.1, U21.7 (B)
unnamed: C96.2, U22.2 (1A)
unnamed: C97.2, U22.1 (1B)
unnamed: C98.2, U22.6 (2A)
unnamed: C99.2, U22.7 (2B)
unnamed: C94.2, U22.14 (4A)
unnamed: C95.2, U22.15 (4B)
unnamed: R148.1, U23.6 (A)
unnamed: R149.1, U23.7 (B)
unnamed: C109.2, U24.2 (1A)
unnamed: C110.2, U24.1 (1B)
unnamed: C111.2, U24.6 (2A)
unnamed: C112.2, U24.7 (2B)
unnamed: C107.2, U24.14 (4A)
unnamed: C108.2, U24.15 (4B)
PCS Charge: JP34.1, U14.46 (GPIO37)
PCS DCDC: JP30.1, U14.42 (GPIO33)
PCS Enable: JP31.1, U14.45 (GPIO36)
PCS IPC CAN RX: JP32.1, U14.44 (GPIO35)
PCS IPC CAN TX: JP33.1, U14.43 (GPIO34)
SUP-MAIN TX/RX: R132.1, TP36.2, U14.78 (GPIO1)
SX Serial RX: D32.1 (K), J3.3, J12.12, R134.2, TP6.2, U14.6 (GPIO8)
SX Serial TX: D27.1 (K), J3.2, J12.10, TP6.1, U14.4 (GPIO7)
Shunt Midpoint: J14.8
Shunt NTC +: C64.2, J14.7, J15.1, R84.1, U17.8 (Vbus)
Shunt Passive +: J14.6
Shunt Sense +: C62.2, J14.5, J15.3, U17.10 (Vin+)
Shunt Sense -: C62.1, J14.4, J15.4, U17.9 (Vin-)
Shunt_3V3: C54.2, C60.2, C116.2, R17.1, R69.1, R72.1, R84.2, TP49.1 (1_1), U16.8 (VCC2), U17.6 (VS), U26.2 (VO); also elsewhere on the board
Shunt_5V: FB3.2, R73.1, TP18.1 (1_1), U26.3 (VI)
Snooper Debug: TP23.2, U14.40 (GPIO32)
Snooper Debug 2: TP44.2, U20.40 (GPIO32)
VContactor Sense: C30.2, R24.1, R25.1, U14.54 (GPIO43_ADC3)
VSenHalf: 1/2V1.1 (1_1), C69.2, C76.1, C77.2, C78.1, C79.2, C80.1, C81.2, R87.2, R88.1, R96.2, R97.1, R98.2, R99.2, R100.2, R101.2
V_{Contactor}: C14.1, C17.2, D16.1 (K), D20.1 (K), D24.2 (A2), D37.1 (K), D38.1 (K), J6.33, J6.34, J6.35, J6.43, J10.1, J10.3, J10.5, J10.7, L2.1, R11.1, R16.1, R24.2, R39.1, R40.1, R152.2
V_{in}: C1.1, C4.2, C6.2, D15.1 (K), R18.2, U3.7 (VIN)
Vin Logic Sense: C23.2, R18.1, R19.1, U14.53 (GPIO42_ADC2)

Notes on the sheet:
all JLC basic components
3.3V 1A LDO Supply
GPIO3 - GPIO12 on NC header
external NC switch for estop, or jumper to disable.
Not tested as of now
I2C ADDR: 0x49
Aux Input 3-5V limited by resistor dissipation for higher input voltage use external series resistor
FC Negative Contactor
Would be cool if it alternates with main
PTC 440V 56Ω
BMB side xfmr center tap has no connection reference to ground to prevent ESD
Use 3v3 so no logic translation necessary.
TX must be on this pin
GND to battery chassis
unused inputs left floating - internal bias
3A max output - 3.3V draws from this rail
1.122V
1.52V
FC positive contactor not used (no 12V connection)
100k input impedance 0.14mA typical ADC usage
Gate driver has internal 200k pullup, 2x in parallel = 100k pullup must pull down to always start in off state.
L must be after H
DIY connector
BMB Connector
MCU Identification
In tesla packs the shunt is at the mid point of the pack and always live!
second ADS1115: 0-1 linkneg - outpos 0-3 linkneg - linkpos <- link voltage 1-3 outpos - linkpos <- voltage across FC pos contactor 2-3 batpos - linkpos <- voltage across battery pos contactor
Supervisor MCU
5V powers exteral ESP32 LCD also
pyro is always live
FC Positive Contactor
Cells to Positive Link Contactor
close to MCU
Aux contacts inside of the FC contactors used to check for welding with or without energizing
Extra GPIO
API TTL RS232 HMI Interface
Redundant connectors
FC negative controls pre-charge bypass
Galvanically Isolated Area
Data must be after En

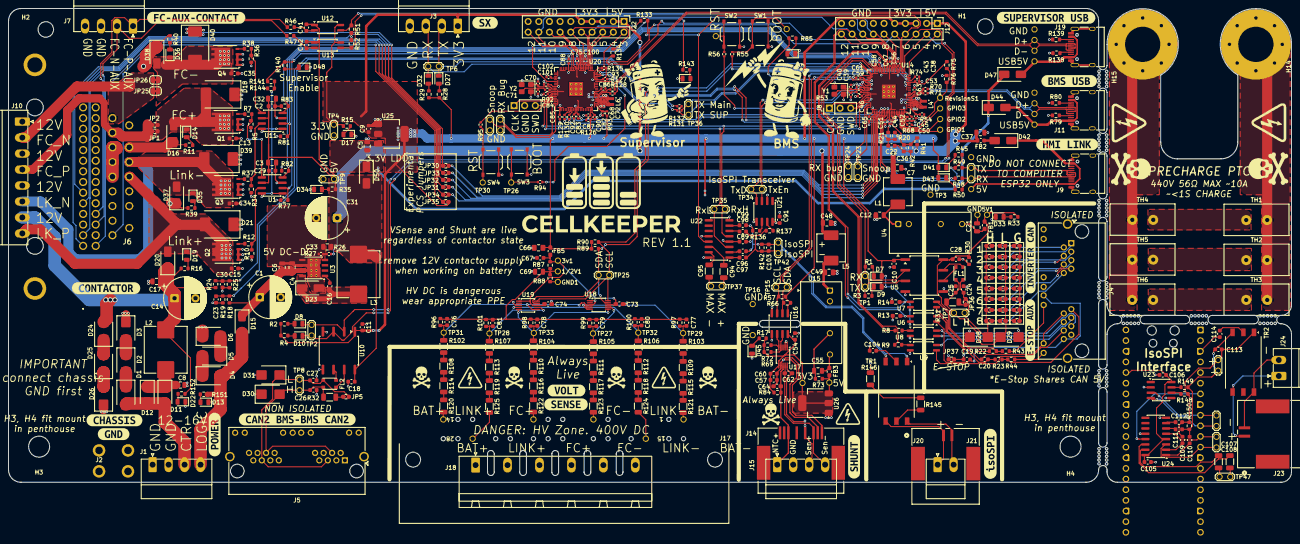
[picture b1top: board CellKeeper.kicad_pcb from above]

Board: 4 copper layers, 306.0 x 113.0 mm, 506 parts (1 on the bottom side), 294 nets.

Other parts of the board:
C57: 1uF; Capacitor_SMD__C_0603_1608Metric
kibuzzard-6A455E05: G***; kibuzzard-6A455E05
kibuzzard-6A455E28: G***; kibuzzard-6A455E28
kibuzzard-6A455E35: G***; kibuzzard-6A455E35
kibuzzard-6A455ED1: G***; kibuzzard-6A455ED1
kibuzzard-6A455F32: G***; kibuzzard-6A455F32
kibuzzard-6A455FAF: G***; kibuzzard-6A455FAF
kibuzzard-6A455FB8: G***; kibuzzard-6A455FB8
kibuzzard-6A4560A1: G***; kibuzzard-6A4560A1
kibuzzard-6A4560DE: G***; kibuzzard-6A4560DE
kibuzzard-6A4561AC: G***; kibuzzard-6A4561AC
kibuzzard-6A6094FF: G***; kibuzzard-6A6094FF
kibuzzard-6A45612B: G***; kibuzzard-6A45612B
kibuzzard-6A45614A: G***; kibuzzard-6A45614A
kibuzzard-6A456096: G***; kibuzzard-6A456096
kibuzzard-6A456143: G***; kibuzzard-6A456143
kibuzzard-6A456164: G***; kibuzzard-6A456164

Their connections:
GND Shunt NTC -: C57.1; also elsewhere on the board
Shunt_3V3: C57.2; also elsewhere on the board

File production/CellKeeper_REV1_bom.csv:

Designator,Footprint,Quantity,Value,LCSC Part #
"1/2V1, 3V1, 5V1, GND1, GPIO1, GPIO2, GPIO3",BMS_Library__TestPoint_THTPad_D1.5mm_Drill1.0mm,7,TP,
A1,Module__RaspberryPi_Pico_Common_Unspecified,1,RaspberryPi_Pico,
"C1, C14, C31",Capacitor_THT__CP_Radial_D10.0mm_P5.00mm,3,680uF,C46550429
"C10, C104, C105, C106, C11, C114, C13, C15, C16, C18, C2, C22, C23, C28, C29, C30, C34, C35, C36, C54, C60, C76, C77, C78, C79, C80, C81, C89, C91",Capacitor_SMD__C_0603_1608Metric,29,100nF,C14663
"C100, C101, C102, C44, C46, C47, C50, C51, C53, C56, C58, C59, C61, C63, C65, C75, C83, C84, C85, C86, C88, C90, C92, C93",Capacitor_SMD__C_0402_1005Metric,24,100n,C1525
"C103, C113, C24, C25, C26, C27",Capacitor_SMD__C_0603_1608Metric,6,100pF,C14858
"C107, C108, C94, C95",Capacitor_SMD__C_1206_3216Metric,4,1nF,C9196
"C109, C110, C111, C112, C19, C20, C41, C42, C57, C67, C96, C97, C98, C99",Capacitor_SMD__C_0603_1608Metric,14,1uF,C15849
"C12, C33, C37, C48, C49, C5, C69, C7",Capacitor_SMD__C_0805_2012Metric,8,22uF,C45783
"C17, C21, C3, C32, C4, C55, C6, C8",Capacitor_SMD__C_0805_2012Metric,8,10uF,C440198
"C38, C43, C68, C72",RP2350_80QFN_minimal__C_0402_1005Metric_small_pads,4,4.7u,C23733
"C39, C40, C70, C71",Capacitor_SMD__C_0402_1005Metric,4,15pF,C1548
"C45, C52, C82, C87",Capacitor_SMD__C_0402_1005Metric,4,4.7u,C23733
"C62, C64, C73, C74",Capacitor_SMD__C_0603_1608Metric_Pad1.08x0.95mm_HandSolder,4,100nf,C14663
C66,Capacitor_SMD__C_0805_2012Metric_Pad1.18x1.45mm_HandSolder,1,10uF,C440198
C9,Capacitor_SMD__C_0603_1608Metric,1,4.7uF,C19666
"D1, D2, D24, D25, D26, D28, D29, D3, D30, D31, D4, D5, D6",Diode_SMD__D_SMB,13,SMB6.8CA,C78395
"D10, D27, D41, D46, D49, D9",LED_SMD__LED_0805_2012Metric,6,Red,C84256
"D11, D12, D15, D16, D20, D23, D37, D38, D42, D44, D47, D50",Diode_SMD__D_SMA,12,SS54,C22452
"D13, D17, D22, D33, D34, D45",LED_SMD__LED_0805_2012Metric,6,White,C34499
"D14, D19, D32, D35, D36, D43, D48, D7, D8",LED_SMD__LED_0805_2012Metric,9,Green,C2297
"D18, D21, D39, D40",Diode_SMD__D_SMC,4,SMCJ33CA,C224050
"FB1, FB3, FB5",Inductor_SMD__L_0603_1608Metric_Pad1.05x0.95mm_HandSolder,3,600R@100MHz,C1002
FB2,Capacitor_SMD__C_0603_1608Metric,1,120Ω@100MHz,C14709
"FL1, FL2",BMS_Library__FILTER-SMD_4P-L3.2-W2.5-BL,2,SDCW3225S-2-102TF,C192586
J1,BMS_Library__PhoenixContact_MC_1_5_4-G-3.81_1x04_P3.81mm_Horizontal_1.4mmPin,1,Screw_Terminal_01x04,
"J11, J19, J9",BMS_Library__USB_C_Receptacle_HRO_TYPE-C-31-M-12,3,USB_C_Receptacle_USB2.0_16P,C2765186
J14,BMS_Library__CONN_ZE05H-8DP-2H_HIR,1,OEM Shunt Connector,C17284895
J17,BMS_Library__CONN_173864-1_TYC_Empty_Pins,1,OEM HV Sense Connector,C573648
J2,BMS_Library__XFCN_T34008_M3_Terminal_Frame_PCB,1,Screw_Terminal_01x01,C481446
"J20, J23",BMS_Library__CONN_SD-34912-001_02_MOL,2,OEM Connector,C587318
"J4, J5",Connector_RJ__RJ45_HCTL_HC-RJ45-5JA-2-2-Y,2,8P8C_LED_Shielded_x2,C3010546
J6,BMS_Library__S44BRAD1AK,1,OEM Connector,
"JP10, JP11, JP15, JP36, JP5, JP6",BMS_Library__J_0603_jumper,6,0r,C21189
"L1, L5",Inductor_SMD__L_Changjiang_FXL0630,2,6.8uh,C167221
"L2, L3",Inductor_SMD__L_Changjiang_FXL1040,2,22uh 5.5A,C475917
"L4, L6",RP2350_80QFN_minimal__L_pol_2016,2,3.3uh,C42411119
"Q1, Q2, Q3, Q4",BMS_Library__TDSON-8_5x6_,4,BSC0805LS,C534374
"R1, R100, R101, R11, R140, R16, R17, R2, R29, R33, R35, R39, R40, R41, R6, R78, R96, R97, R98, R99",Resistor_SMD__R_0603_1608Metric,20,24k,C23352
"R10, R18, R24, R34, R36, R5",Resistor_SMD__R_0603_1608Metric,6,100k,C25803
"R102, R103, R104, R105, R106, R107, R108, R109, R110, R111, R112, R113, R114, R115, R116, R117, R118, R119, R120, R121, R122, R123, R124, R125",Resistor_SMD__R_1206_3216Metric,24,3M,C488822
"R12, R37, R38, R7",Resistor_SMD__R_0603_1608Metric,4,33R,C23140
"R126, R54, R68, R93",Resistor_SMD__R_0402_1005Metric,4,33r,C25105
"R127, R128, R70, R71",Resistor_SMD__R_0402_1005Metric,4,22R,C25092
"R129, R130, R131, R132, R135, R27, R53, R55, R56, R74, R92, R94, R95",Resistor_SMD__R_0402_1005Metric,13,1k,C11702
"R13, R14, R51, R52",Resistor_SMD__R_0603_1608Metric_Pad0.98x0.95mm_HandSolder,4,10k,C25804
"R133, R134, R141, R22, R23, R46, R47, R48, R49, R8, R9",Resistor_SMD__R_0603_1608Metric,11,1k,C21190
"R136, R137, R148, R149",Resistor_SMD__R_0603_1608Metric,4,47r,C23182
"R138, R139, R143, R144, R45, R57, R66, R69, R72, R77, R79, R80, R81, R82, R83, R85, R89, R90",Resistor_SMD__R_0603_1608Metric,18,5.1k,C23186
"R142, R150",Resistor_SMD__R_0603_1608Metric,2,100R,C22775
"R145, R146",Resistor_SMD__R_1206_3216Metric,2,1M,C17927
"R15, R19, R20, R21, R25, R28, R3, R4, R42, R50, R84",Resistor_SMD__R_0603_1608Metric,11,10k,C25804
R26,Resistor_SMD__R_0402_1005Metric,1,3.3k,C25890
"R30, R73",Resistor_SMD__R_0603_1608Metric,2,510r,C23193
"R31, R32",Resistor_SMD__R_1206_3216Metric,2,120r,C17909
"R43, R44",Resistor_SMD__R_0603_1608Metric,2,2.2k,C4190
R76,Resistor_SMD__R_0603_1608Metric,1,0r,C21189
"R87, R88",Resistor_SMD__R_0603_1608Metric,2,220r,C22962
"SW1, SW2, SW3, SW4",Button_Switch_SMD__SW_Push_1P1T_XKB_TS-1187A,4,TS-1187A-B-A-B,C318884
"TH1, TH2, TH3, TH4, TH5, TH6",BMS_Library__RV_Disc_D15.5mm_W7.5mm_P5.0mm,6,B59451C1130B070,C2762811
"TR1, TR2",BMS_Library__HM2113ZNLT,2,HM2113ZNLT,C5730533
"U1, U11",Package_SO__SOIC-8_3.9x4.9mm_P1.27mm,2,UCC27524DR,C465729
"U10, U5",Package_SO__SOP-8_6.62x9.15mm_P2.54mm,2,ISO1050DUB,C16428
"U12, U13, U6, U7, U8, U9",Package_SO__SSOP-4_4.4x2.6mm_P1.27mm,6,LTV-217-B-G,C115450
"U14, U20",RP2350_80QFN_minimal__RP2350-QFN-80-1EP_10x10_P0.4mm_EP3.4x3.4mm_ThermalVias,2,RP2354B,C39843328
"U15, U4",BMS_Library__H0505S-1WR2,2,F0505S-1WR3,C7465182
U16,Package_SO__SOIC-8_3.9x4.9mm_P1.27mm,1,ISO1540,C179739
U17,Package_SO__TSSOP-10_3x3mm_P0.5mm,1,INA228,C5214669
"U18, U19",Package_SO__TSSOP-10_3x3mm_P0.5mm,2,ADS1115,C37593
U2,Package_TO_SOT_SMD__SOT-223-3_TabPin2,1,AMS1117-3.3,C6186
"U21, U23",Package_SO__SOIC-8_3.9x4.9mm_P1.27mm,2,SP3485EN-L/TR,C8963
"U22, U24",Package_SO__SOIC-16_3.9x9.9mm_P1.27mm,2,AM26LV32EIDR,C527448
U3,Package_SO__TI_SO-PowerPAD-8_ThermalVias,1,TPS5430DDAR,C9864
"Y1, Y2",Crystal__Crystal_SMD_3225-4Pin_3.2x2.5mm,2,ABM8-272-T3,C20625731
